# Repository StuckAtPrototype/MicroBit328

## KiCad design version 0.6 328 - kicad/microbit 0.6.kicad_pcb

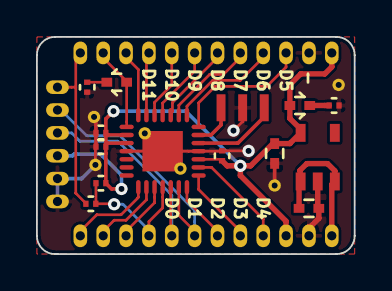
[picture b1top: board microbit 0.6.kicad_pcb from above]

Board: 2 copper layers, 17.7 x 12.1 mm, 23 parts (0 on the bottom side), 26 nets.

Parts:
C1, C2, C3, C6: 0.1uF; C_0201
C4: 1uF; C_0402
C5: 2.2uF; C_0402
D1: RED; LED_0402
D2: BLUE; LED_0402
J1: MB_Header_12_A; Header_50mil_12
J2: MB_Header_12_B; Header_50mil_12
J3: FTDI; Header_50mil_6
Q1: 16MHz; CSTCE16M0V53-R0
R1, R3: 2.7k; C_0201
R2: 10k; C_0201
STICHING_VIA11, STICHING_VIA13, STICHING_VIA14, STICHING_VIA15, STICHING_VIA22, STICHING_VIA23: VAL**; STICHING_VIA
U1: Atmega328p_MMHR
U2: LP2985-50DBVR

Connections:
+5V: C1.1, C2.1, C3.1, C5.1, D1.1, J1.12, J2.10, J3.3, R2.2, U1.3, U1.16, U1.17, U2.5
GND: C1.2, C2.2, C3.2, C4.2, C5.2, J1.11, J2.11, J3.1, J3.2, Q1.2, R1.2, R3.2, STICHING_VIA11.1, STICHING_VIA13.1, STICHING_VIA14.1, STICHING_VIA15.1, STICHING_VIA22.1, STICHING_VIA23.1, U1.4, U1.18, U1.29, U2.2
unnamed: C4.1, J2.12, U2.1, U2.3
unnamed: C6.1, J2.4, R2.1, U1.25
unnamed: C6.2, J1.1, J3.6
unnamed: D1.2, R1.1
unnamed: D2.1, J1.2, U1.15
unnamed: D2.2, R3.1
unnamed: J1.3, U1.14
unnamed: J1.4, U1.13
unnamed: J1.5, U1.12
unnamed: J1.6, U1.11
unnamed: J1.7, U1.10
unnamed: J1.8, U1.9
unnamed: J1.9, U1.8
unnamed: J1.10, U1.7
unnamed: J2.1, U1.22
unnamed: J2.2, U1.23
unnamed: J2.3, U1.24
unnamed: J2.5, J3.4, U1.26
unnamed: J2.6, J3.5, U1.27
unnamed: J2.7, U1.28
unnamed: J2.8, U1.1
unnamed: J2.9, U1.2
unnamed: Q1.1, U1.5
unnamed: Q1.3, U1.6

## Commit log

2025-11-18 open sourced!
2025-11-19 removed unnecessary files
